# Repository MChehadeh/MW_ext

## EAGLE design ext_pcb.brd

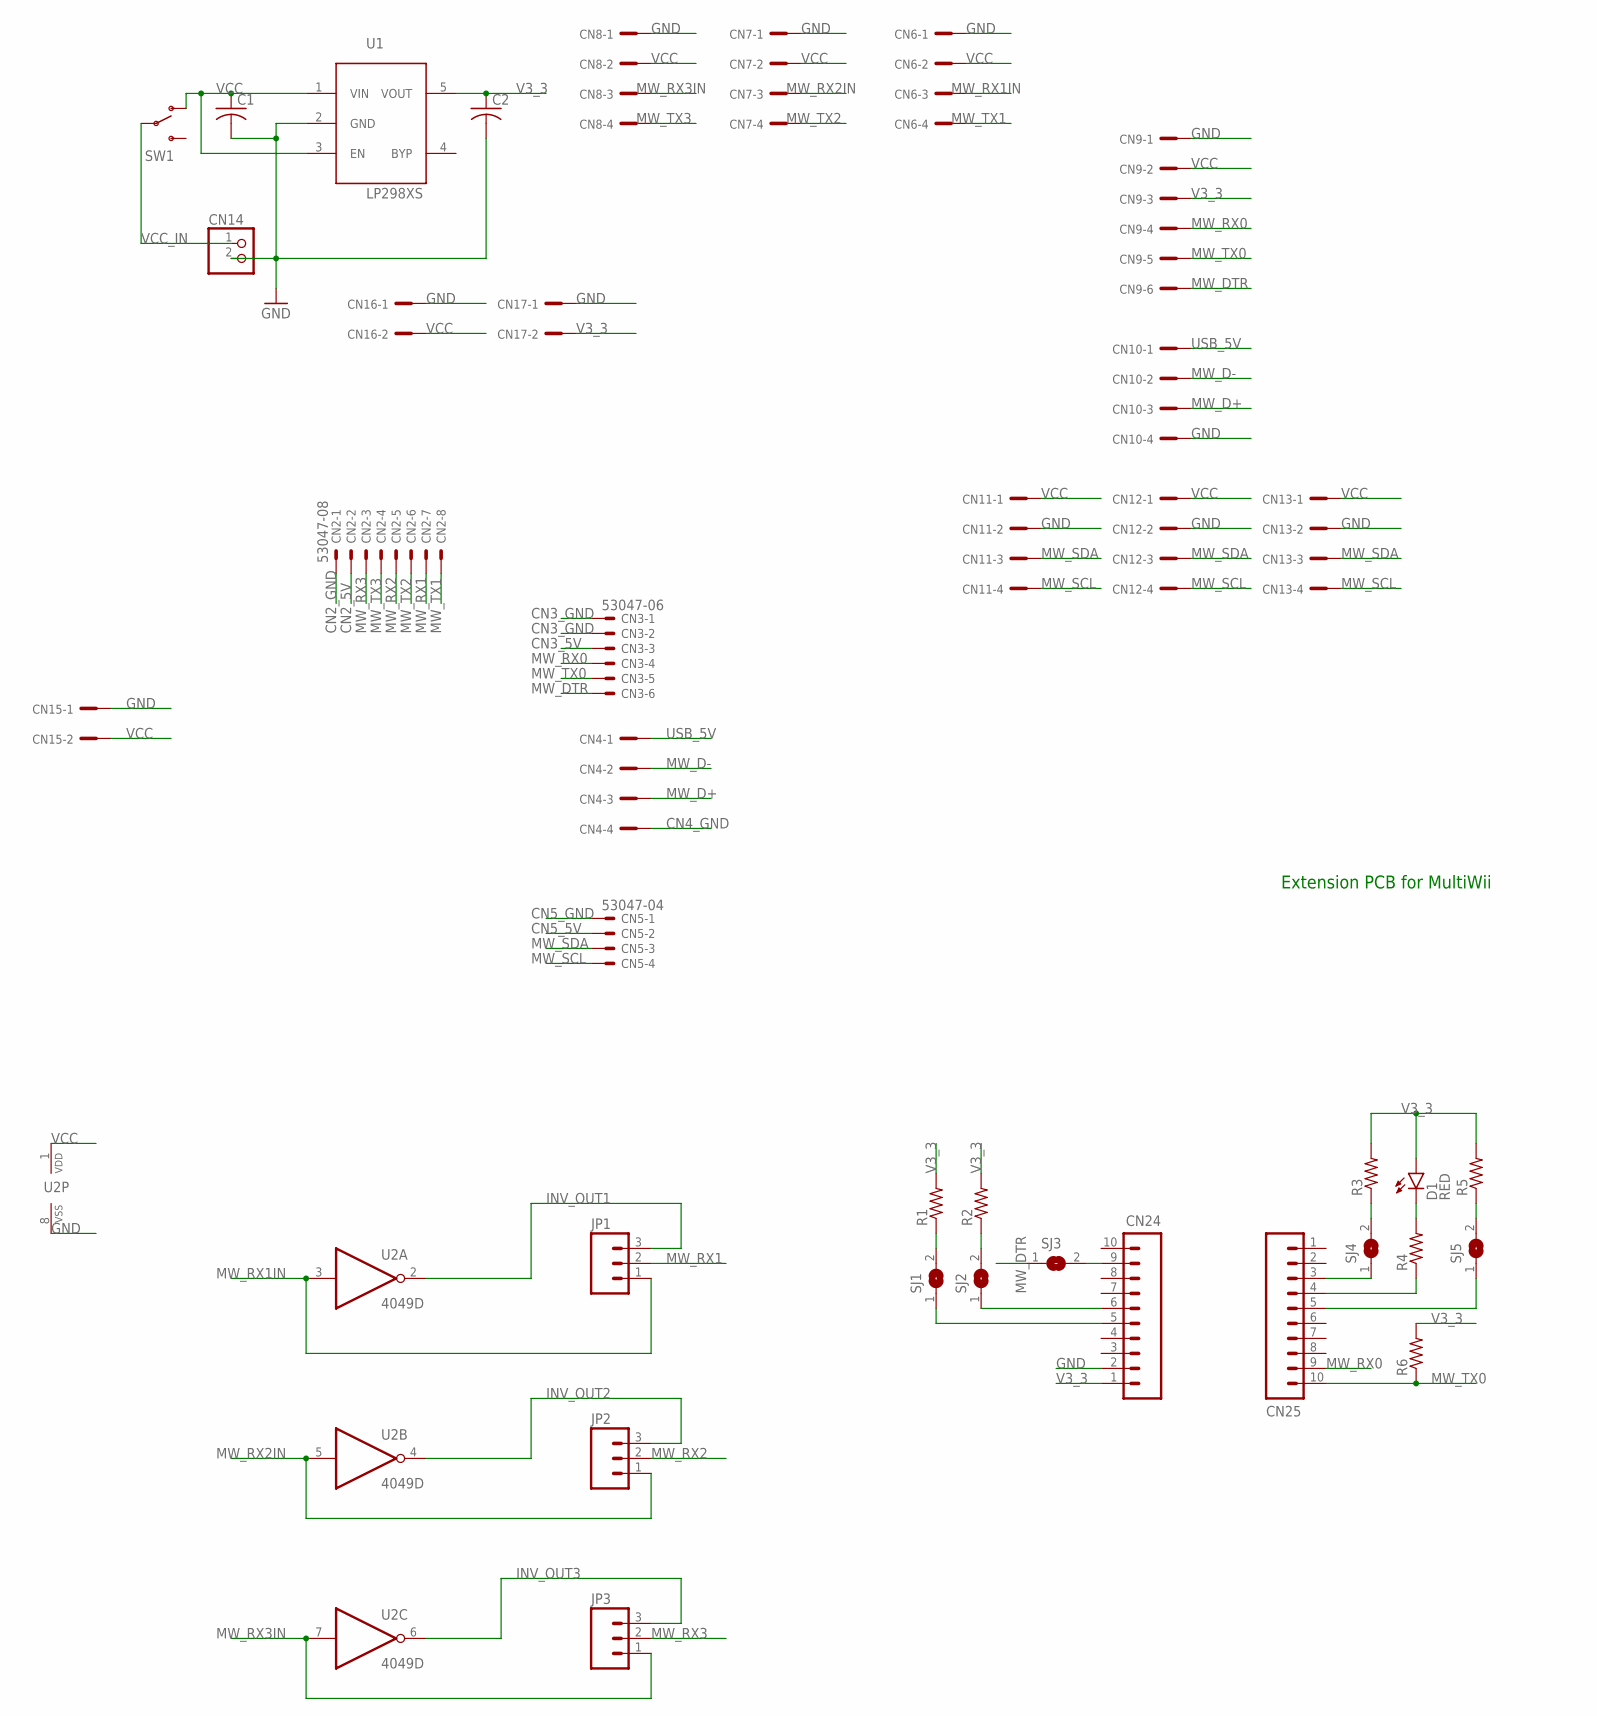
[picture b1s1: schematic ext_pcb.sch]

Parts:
C1, C2: C-USC0805; C0805
CN2: 53047-08
CN3: 53047-06
CN4, CN6, CN7, CN8, CN10, CN11, CN12, CN13: MCV_05/4-G-2,5V; MCV4
CN5: 53047-04
CN9: MCV_05/6-G-2,5V; MCV6
CN14: PINHD-1X2; 1X02
CN15, CN16, CN17: MCV_05/2-G-2,5V; MCV2
CN24, CN25: M10SILK_FEMALE_PTH; 1X10
D1: RED; LED-1206
JP1, JP2, JP3: M03PTH; 1X03
R1, R2, R3, R4, R5, R6: RESISTOR0805-RES; 0805
SJ1, SJ2, SJ3, SJ4, SJ5: SJW
SW1: SWITCH-SPDTPTH; SWITCH-SPDT
U1: LP298XS; SOT23-5L
U2: 4049D; SO16

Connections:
CN2_5V: CN2.2
CN2_GND: CN2.1
CN3_5V: CN3.3
CN3_GND: CN3.1, CN3.2
CN4_GND: CN4.4
CN5_5V: CN5.2
CN5_GND: CN5.1
GND: C1.2, C2.2, CN6.1, CN7.1, CN8.1, CN9.1, CN10.4, CN11.2, CN12.2, CN13.2, CN14.2, CN15.1, CN16.1, CN17.1, CN24.2, U1.2 (GND), U2.8 (VSS)
INV_OUT1: JP1.3, U2.2 (O)
INV_OUT2: JP2.3, U2.4 (O)
INV_OUT3: JP3.3, U2.6 (O)
MW_D+: CN4.3, CN10.3
MW_D-: CN4.2, CN10.2
MW_DTR: CN3.6, CN9.6, SJ3.1
MW_RX0: CN3.4, CN9.4, CN25.9
MW_RX1: CN2.7, JP1.2
MW_RX1IN: CN6.3, JP1.1, U2.3 (I)
MW_RX2: CN2.5, JP2.2
MW_RX2IN: CN7.3, JP2.1, U2.5 (I)
MW_RX3: CN2.3, JP3.2
MW_RX3IN: CN8.3, JP3.1, U2.7 (I)
MW_SCL: CN5.4, CN11.4, CN12.4, CN13.4
MW_SDA: CN5.3, CN11.3, CN12.3, CN13.3
MW_TX0: CN3.5, CN9.5, CN25.10, R6.1
MW_TX1: CN2.8, CN6.4
MW_TX2: CN2.6, CN7.4
MW_TX3: CN2.4, CN8.4
unnamed: CN24.9, SJ3.2
unnamed: CN24.6, SJ2.1
unnamed: CN24.5, SJ1.1
unnamed: R1.1, SJ1.2
unnamed: R2.1, SJ2.2
unnamed: CN25.3, SJ4.1
unnamed: R3.1, SJ4.2
unnamed: D1.C, R4.2
unnamed: R5.1, SJ5.2
unnamed: CN25.4, R4.1
unnamed: CN25.5, SJ5.1
USB_5V: CN4.1, CN10.1
V3_3: C2.1, CN9.3, CN17.2, CN24.1, D1.A, R1.2, R2.2, R3.2, R5.2, R6.2, U1.5 (VOUT)
VCC: C1.1, CN6.2, CN7.2, CN8.2, CN9.2, CN11.1, CN12.1, CN13.1, CN15.2, CN16.2, SW1.1 (O), U1.1 (VIN), U1.3 (EN), U2.1 (VDD)
VCC_IN: CN14.1, SW1.2

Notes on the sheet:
Extension PCB for MultiWii

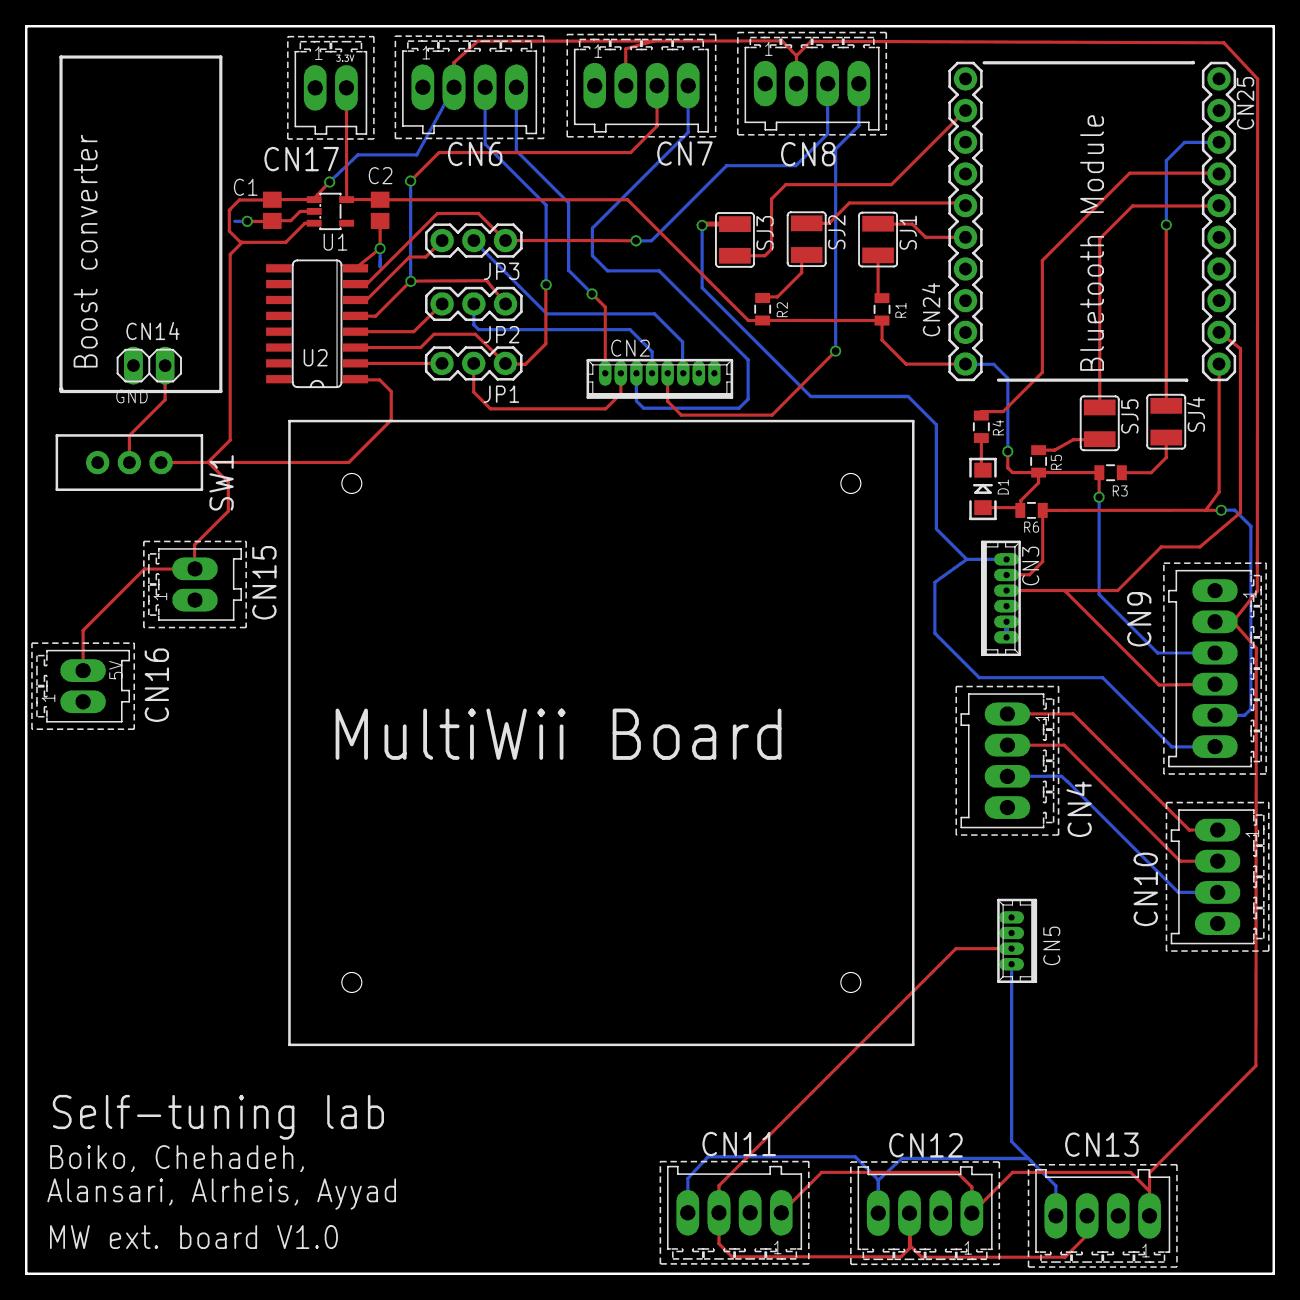
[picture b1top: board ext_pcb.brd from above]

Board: 2 copper layers, 100.0 x 100.0 mm, 38 parts (0 on the bottom side), 36 nets.

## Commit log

2015-12-30 $$ Initial commit on Git $$
2015-12-30 Change ground connections
2016-01-01 Finish PCB traces
2016-01-01 First Draft PCB Design
2016-01-02 Final Draft
2016-01-03 Revised Version 1
2016-01-04 %% Purchase plan (BOM) added %%
2016-01-04 Final Version Sent to Manufacturer
2016-01-04 Changes to purchase_plan.xlsx --new purchases from mouser, seeedstudio, and ebay

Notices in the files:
parts and their libraries:
SparkFun-Connectors: Licensing: Creative Commons ShareAlike 4.0 International - https://creativecommons.org/licenses/by-sa/4.0
